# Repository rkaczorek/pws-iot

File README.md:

# pws-iot
Personal Weather Station IoT. It reads various environmental sensors and publishes values to MQTT server via wireless connection.

# Features
- Weather Sensors
    - Temperature
    - Humidity
    - Pressure
    - Dew Point
    - Wind Speed
    - Wind Gust
    - Wind Direction
    - Rain Gauge
    - Clouds
    - Light
- WiFi connection
- MQTT messaging
- Manual or Auto polling
- Home Assistant integration

# Requirements
- MQTT server
- Node-Red (optional - only for routing data to InfluxDB)
- InfluxDB (optional - only for data persistency)

# Supported MCUs
- Arduino Nano 33 IoT
- Arduino MKR WiFi 1000
- Arduino MKR WiFi 1010
- Arduino Uno Wifi Rev2
- ESP8266

# Supported GPIO connected (A0, D10, D11) sensors
- Weather Meters (wind direction, wind speed, rainfall) (https://www.sparkfun.com/products/8942)

# Supported I2C sensors
- BME280 (temperature, humidity, pressure)
- MLX90614 (ambient temperature, object temperature)
- VEML7700 (light)

# Home Assistant
You can easily integrate Personal Weather Station IoT with your Home Assistant.
Just make sure that MQTT Integration is installed on Home Assistant. We are using Home Assistant 
autodiscovery feature to add Personal Weather Station device and sensor entities automatically.

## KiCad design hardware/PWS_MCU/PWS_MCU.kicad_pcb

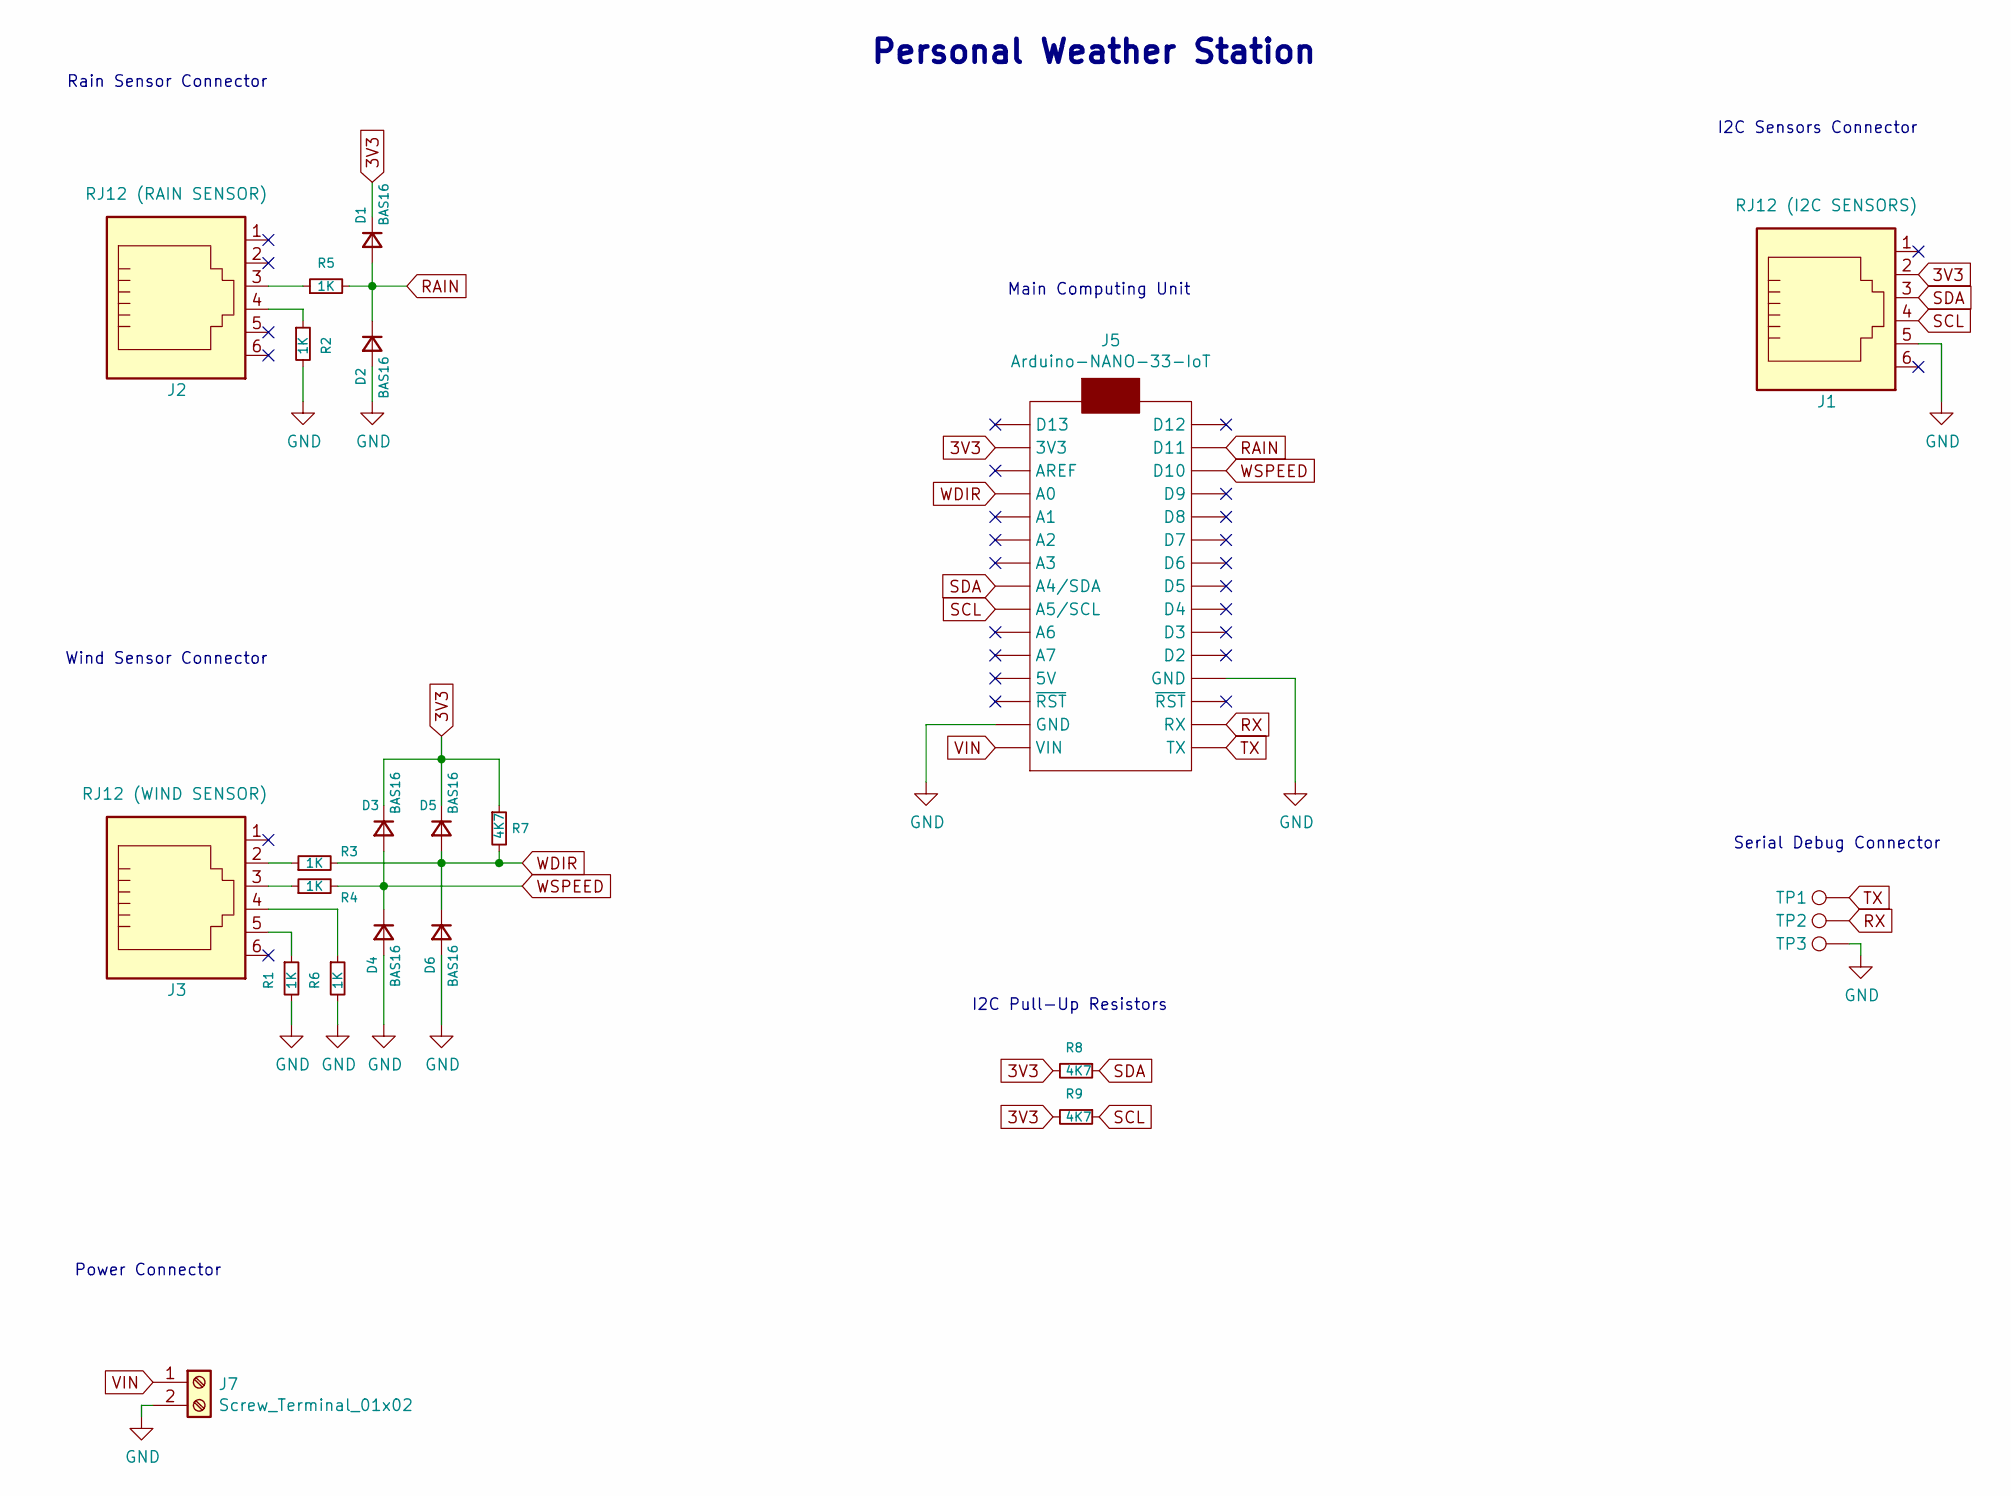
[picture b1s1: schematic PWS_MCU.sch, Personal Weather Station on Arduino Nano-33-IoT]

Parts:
D1, D2, D3, D4, D5, D6: BAS16; D_SOD-123
J1: RJ12 (I2C SENSORS); molex_6p6c
J2: RJ12 (RAIN SENSOR); molex_6p6c
J3: RJ12 (WIND SENSOR); molex_6p6c
J5: Arduino-NANO-33-IoT; NANO_33_Footprint_SMD_Castell
J7: Screw_Terminal_01x02; TerminalBlock_Phoenix_MPT-2.54mm_2pol
R1, R2, R3, R4, R5, R6: 1K; R_0603_HandSoldering
R7, R8, R9: 4K7; R_0603_HandSoldering
TP1, TP2, TP3: TestPoint; Measurement_Point_Square-SMD-Pad_Small

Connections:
3V3: D1.1 (K), D3.1 (K), D5.1 (K), J1.2, J5.2 (3V3), R7.1, R8.2, R9.2
GND: D2.2 (A), D4.2 (A), D6.2 (A), J1.5, J5.14 (GND), J5.19 (GND), J7.2, R1.2, R2.2, R6.2, TP3.1
unnamed: J2.3, R5.1
unnamed: J2.4, R2.1
unnamed: J3.2, R3.1
unnamed: J3.3, R4.1
unnamed: J3.4, R6.1
unnamed: J3.5, R1.1
RAIN: D1.2 (A), D2.1 (K), J5.29 (D11), R5.2
RX: J5.17 (RX), TP2.1
SCL: J1.4, J5.9 (A5/SCL), R9.1
SDA: J1.3, J5.8 (A4/SDA), R8.1
TX: J5.16 (TX), TP1.1
VIN: J5.15 (VIN), J7.1
WDIR: D5.2 (A), D6.1 (K), J5.4 (A0), R3.2, R7.2
WSPEED: D3.2 (A), D4.1 (K), J5.28 (D10), R4.2

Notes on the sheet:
Main Computing Unit
Rain Sensor Connector
Wind Sensor Connector
I2C Pull-Up Resistors
I2C Sensors Connector
Serial Debug Connector
Personal Weather Station
Power Connector

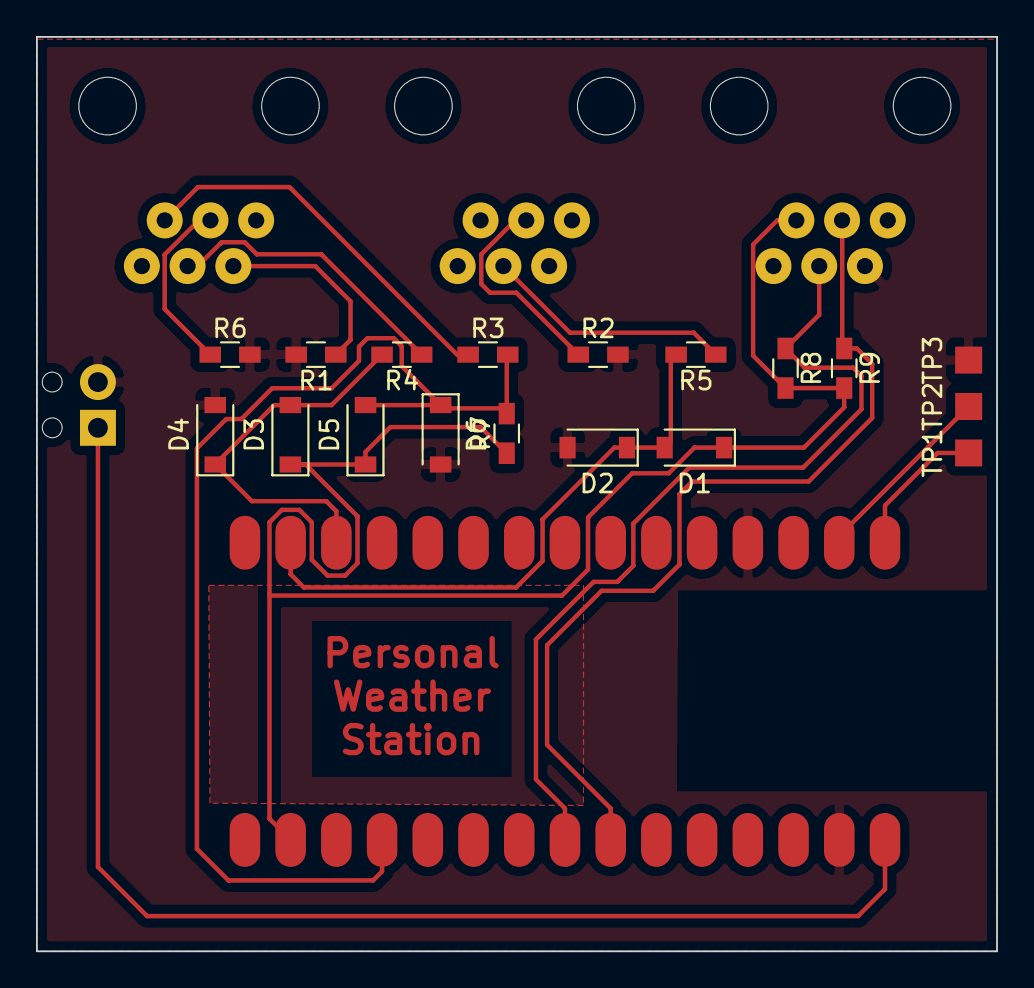
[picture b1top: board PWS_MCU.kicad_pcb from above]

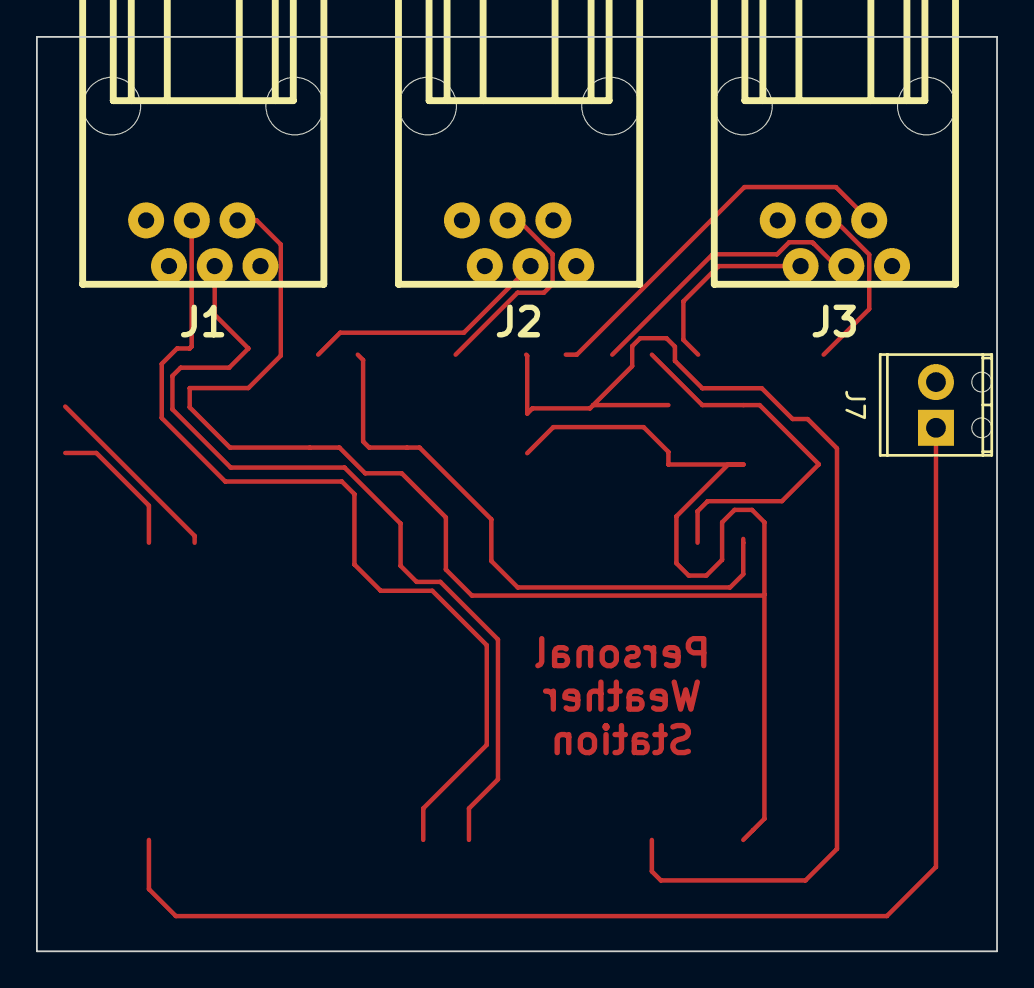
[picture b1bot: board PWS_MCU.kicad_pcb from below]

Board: 2 copper layers, 53.3 x 50.8 mm, 23 parts (4 on the bottom side), 16 nets.

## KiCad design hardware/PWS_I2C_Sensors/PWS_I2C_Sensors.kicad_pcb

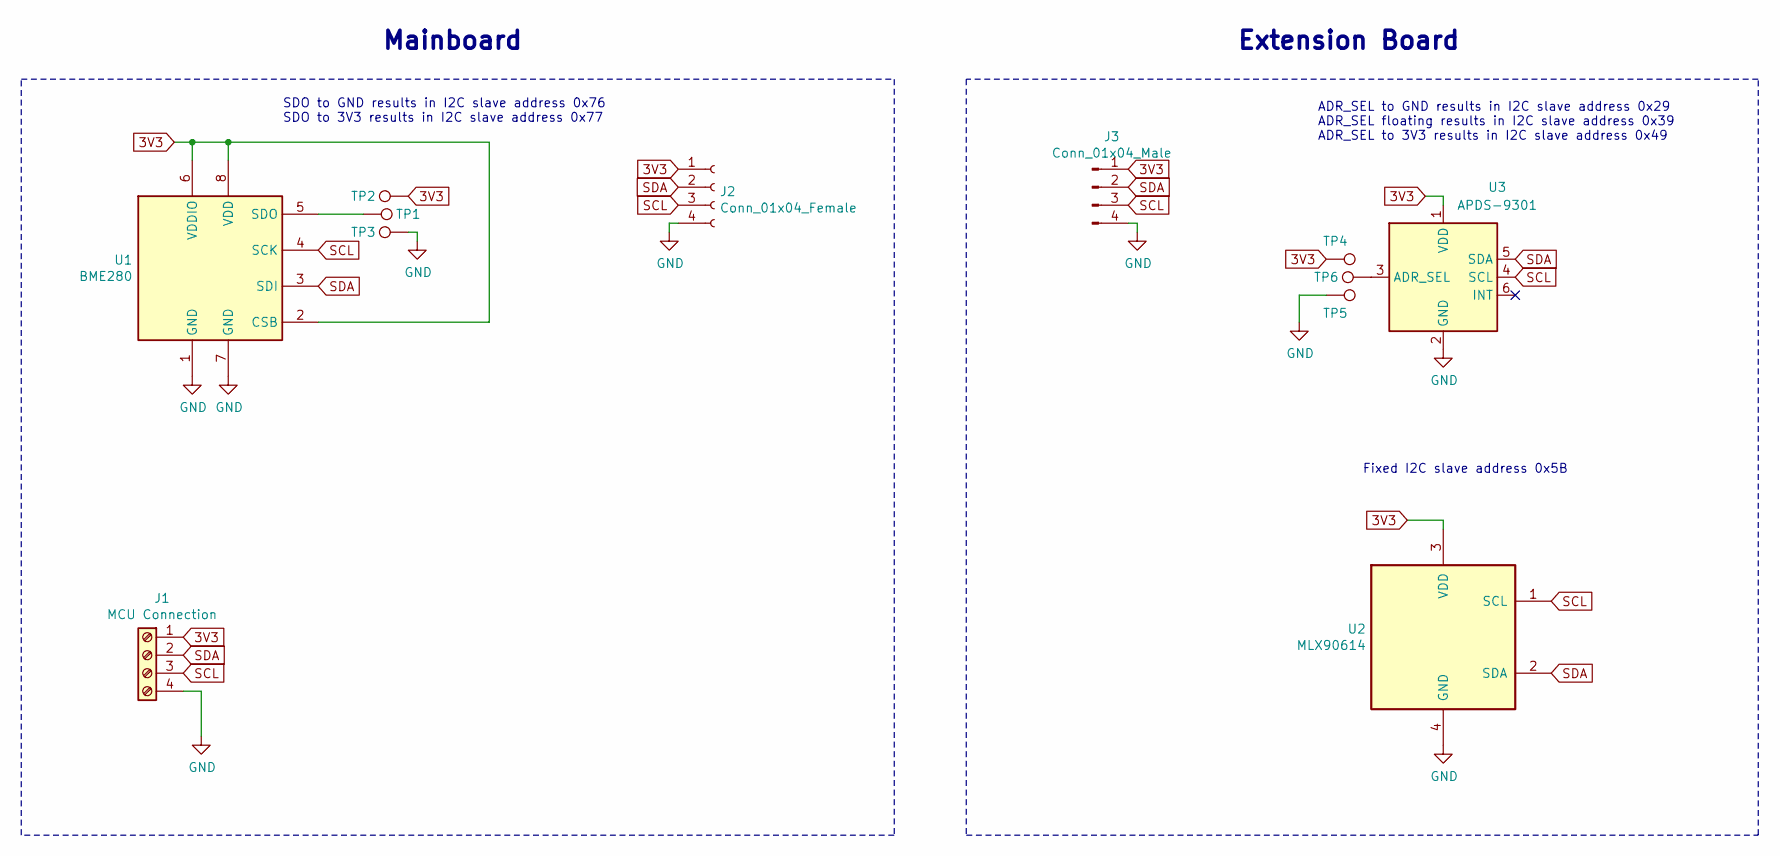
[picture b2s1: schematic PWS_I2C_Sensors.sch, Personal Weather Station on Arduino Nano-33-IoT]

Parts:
J1: MCU Connection; TerminalBlock_Phoenix_MPT-2.54mm_4pol
J2: Conn_01x04_Female; Pin_Header_Angled_1x04_Pitch2.54mm
J3: Conn_01x04_Male; Pin_Header_Straight_1x04_Pitch2.54mm
TP1, TP2, TP3, TP4, TP5, TP6: TestPoint; Measurement_Point_Square-SMD-Pad_Small
U1: BME280; Bosch_LGA-8_2.5x2.5mm_Pitch0.65mm_ClockwisePinNumbering
U2: MLX90614
U3: APDS-9301; Broadcom_APDS-9301

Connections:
3V3: J1.1, J2.1, J3.1, TP2.1, TP4.1, U1.2 (CSB), U1.6 (VDDIO), U1.8 (VDD), U2.3 (VDD), U3.1 (VDD)
GND: J1.4, J2.4, J3.4, TP3.1, TP5.1, U1.1 (GND), U1.7 (GND), U2.4 (GND), U3.2 (GND)
unnamed: TP1.1, U1.5 (SDO)
unnamed: TP6.1, U3.3 (ADR_SEL)
SCL: J1.3, J2.3, J3.3, U1.4 (SCK), U2.1 (SCL), U3.4 (SCL)
SDA: J1.2, J2.2, J3.2, U1.3 (SDI), U2.2 (SDA), U3.5 (SDA)

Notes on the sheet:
Mainboard
Extension Board
SDO to GND results in I2C slave address 0x76 SDO to 3V3 results in I2C slave address 0x77
ADR_SEL to GND results in I2C slave address 0x29 ADR_SEL floating results in I2C slave address 0x39 ADR_SEL to 3V3 results in I2C slave address 0x49
Fixed I2C slave address 0x5B

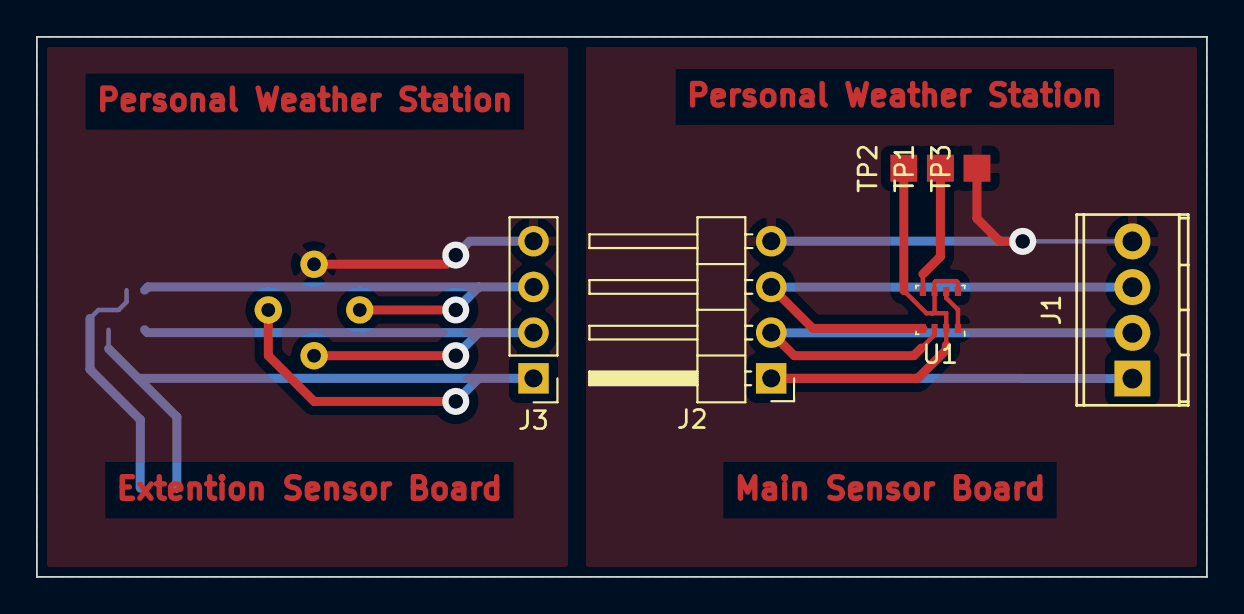
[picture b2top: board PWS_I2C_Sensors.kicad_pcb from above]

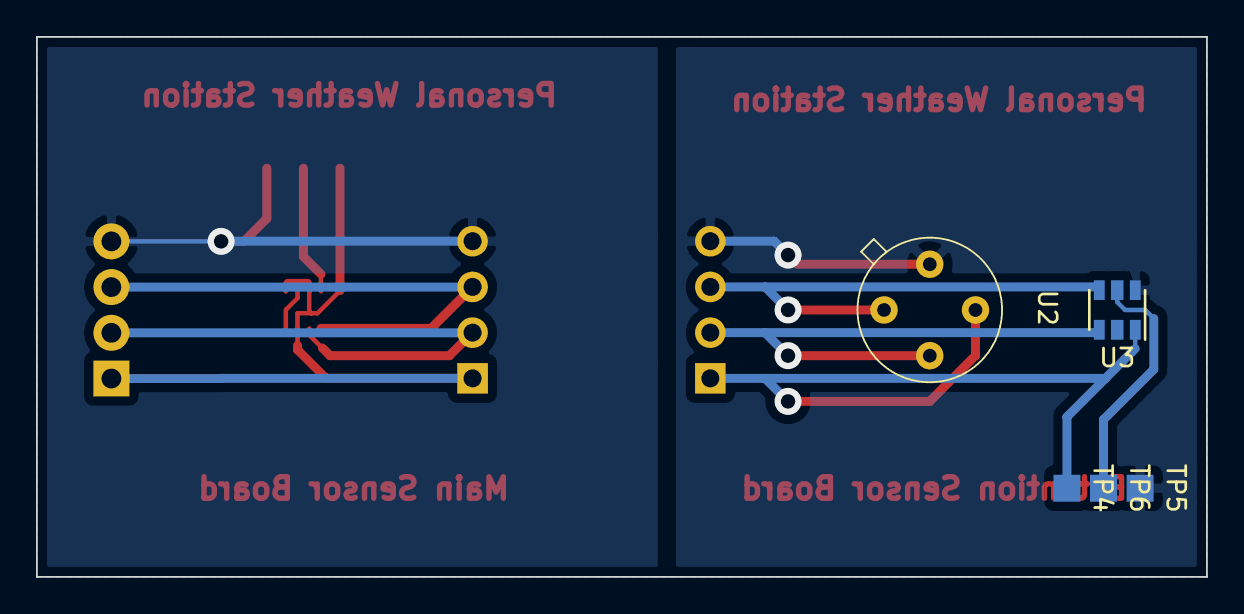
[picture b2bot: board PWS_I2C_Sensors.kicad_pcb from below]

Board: 2 copper layers, 65.0 x 30.0 mm, 12 parts (5 on the bottom side), 6 nets.

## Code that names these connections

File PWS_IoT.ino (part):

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// ===================================================================

// hardware pins definitions
const byte WDIR = A0;
const byte WSPEED = 10;
const byte RAINFALL = 11;

// volatiles are subject to modification by IRQs
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
void setup() {
  pinMode(LED_BUILTIN, OUTPUT); // led
  pinMode(WDIR, INPUT); // input from winddir sensor
  pinMode(WSPEED, INPUT_PULLUP); // input from windspeed sensor
  pinMode(RAINFALL, INPUT_PULLUP); // input from rain gauge sensor

  // attach external interrupt pins to IRQ functions
  attachInterrupt(digitalPinToInterrupt(RAINFALL), rainfallIRQ, FALLING);
  attachInterrupt(digitalPinToInterrupt(WSPEED), windspeedIRQ, FALLING);

  // turn on interrupts
  interrupts();
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    /*
    Rain gauge provides buckets which measure 0.2794 mm (0.011") of rainfall for each click.

    Light rain - less than 2.5 mm/h (<0.1”/hr) or <0.04 mm/min (<0.0007”/min) rain rate, which is 9 full tipping buckets per hour (9 pulses/hr).    
    Moderate rain - rain rate of fall is 2.6 to 7.5 mm/h (0.1 to 0.3”/hr) or 0.04 to 0.125 mm/min (0.0017 to 0.005”/hr), which is 10 to 27 full tipping buckets per hour (10 to 27 pulses/hr).
    Heavy rain - rain rate is greater than 7.6 to 50 mm/h (0.3 to 2”/hr) or 0.125 to 0.83 mm/min (0.005" to 0.033”/min), which is 28 or more full tipping buckets per hour (28+ pulses/hr).
    Violent rain - rain rate grater than >50 mm/hr (>2 in/hr) or >0.83 mm/min (>0.033”/min), which is 180 or more full tipping buckets per hour (180+ pulses/hr, 3+ pulses/minute).

    Note: Rainfall intensity calculation (mm/h or mm/min) must be handled on client side. PWS IoT returns only raw rainfall values in mm every N seconds, where N = configurable polling time.
    */
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
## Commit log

2022-02-24 Release v1.0
2022-02-24 Housekeeping
2022-02-24 Misc files added
2022-02-24 Screenshot added
2022-02-24 Inline comments updated
2022-02-24 Readme updated
2022-02-24 License updated
2022-04-01 Adding maximum wind speeds
2023-04-13 Fix rainfall precision
2023-04-15 HA MQTT Integration added. Code refactoring
2023-04-18 MQTT improvement and fixes
2023-04-18 Agregating wind sensors
2023-04-18 Change default polling time for better UX
2023-06-08 Major refactoring
2023-06-08 Improving MQTT retain & QOS handling
2023-06-08 Update changelog
2024-03-18 Home Assistant integration improvements
2024-03-18 Version change
2024-05-02 HA support improved. Autorestart if wifi connection lost
2024-06-01 Code refactoring for WiFi and MQTT. Command interface added
2024-06-03 Telnet debug added. Sanity check for VEML added.
2024-06-03 SparkFunMLX90614 replaced by Adafruit_MLX90614
2024-06-03 Renaming telnet debug function
2024-06-03 Telnet debug improvements
2024-06-05 Cleaning variable types for purity
2024-06-05 Updating Json calls
2024-06-05 Unix timestamp added to telnet debug
2024-06-05 Ensuring that we're online
2024-06-05 Debugging improvement. Command handling added
2024-06-05 Updating header file

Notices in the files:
PWS_IoT.ino:
By: Radek Kaczorek, (C) 2021 - 2024
License: GNU General Public License v3.0
